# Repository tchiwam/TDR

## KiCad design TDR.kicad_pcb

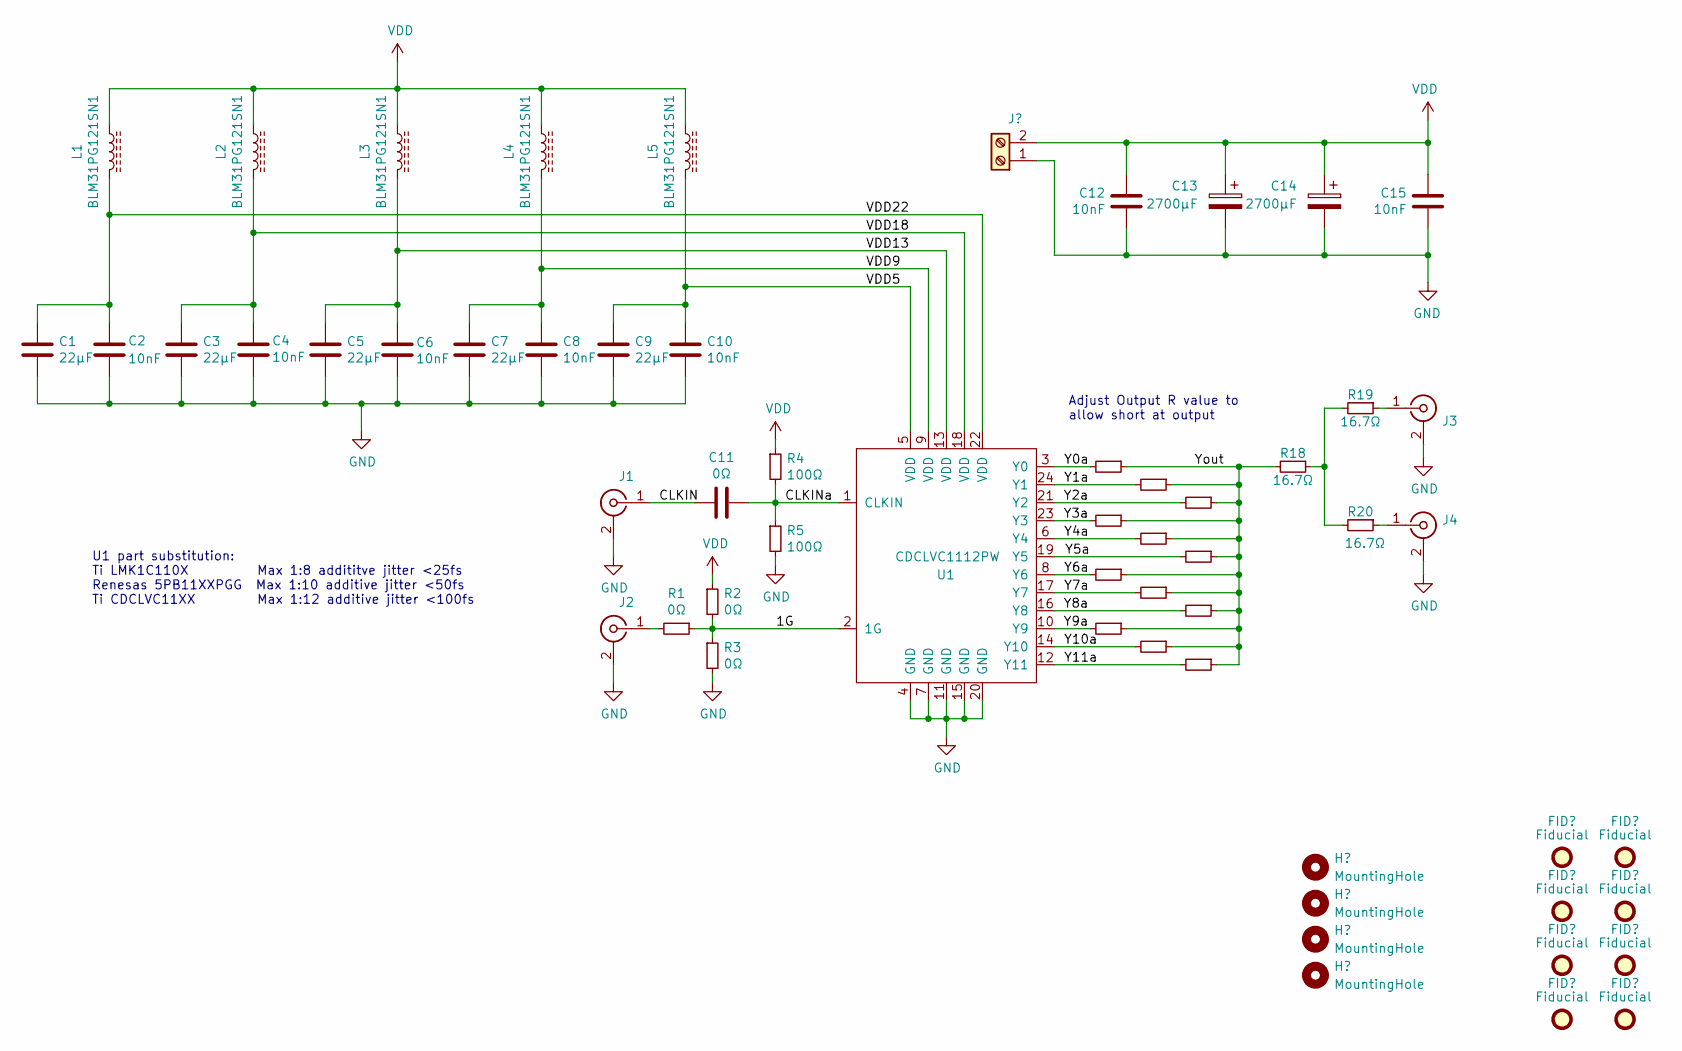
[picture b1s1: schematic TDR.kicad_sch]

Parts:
C1, C3, C5, C7, C9: 22µF; C_1206_3216Metric; PartNumber LMK316AB7226KL-TR
C2, C4, C6, C8, C10, C12, C15: 10nF; C_0402_1005Metric; PartNumber 0402ZC103JAT2A
C11: 0Ω; C_0402_1005Metric; PartNumber ERJ-2GE0R00X
C13, C14: 2700µF; CP_Elec_10x12.6; PartNumber PCG0G272MCL1GS
J1: Conn_Coaxial; SMA_Molex_73251-2123_EdgeMount_Horizontal; PartNumber 73412-0110
J2: Conn_Coaxial; U.FL_Molex_MCRF_73412-0110_Vertical; PartNumber 73412-0110
J3, J4: Conn_Coaxial; SMA_Molex_73251-2123_EdgeMount_Horizontal; PartNumber 73251-2123
L1, L2, L3, L4, L5: BLM31PG121SN1; L_1206_3216Metric; PartNumber ILHB1206ER121V
R1, R2, R3: 0Ω; R_0402_1005Metric; PartNumber ERJ-2GE0R00X
R4, R5: 100Ω; R_0402_1005Metric; PartNumber CR0402-16W-1000FT
R6, R7, R8, R9, R10, R11, R12, R13, R14, R15, R16, R17: 421Ω; R_0402_1005Metric; PartNumber ERJ-2GEJ100X
R18: 16.7Ω; R_1210_3225Metric; PartNumber ERJ-2GEJ100X
R19, R20: 16.7Ω; R_0805_2012Metric; PartNumber ERJ-2GEJ100X
U1: CDCLVC1112PW‎; TSSOP-24_4.4x7.8mm_P0.65mm; PartNumber CDCLVC1112PW‎

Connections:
/1G: R1.1, R2.2, R3.1, U1.2 (1G)
/CLKIN: C11.2, J1.1 (In)
/CLKINa: C11.1, R4.2, R5.1, U1.1 (CLKIN)
/VDD5: C9.1, C10.1, L5.2, U1.5 (VDD)
/VDD9: C7.1, C8.1, L4.2, U1.9 (VDD)
/VDD13: C5.1, C6.1, L3.2, U1.13 (VDD)
/VDD18: C3.1, C4.1, L2.2, U1.18 (VDD)
/VDD22: C1.1, C2.1, L1.2, U1.22 (VDD)
/Y0a: R6.2, U1.3 (Y0)
/Y1a: R10.2, U1.24 (Y1)
/Y2a: R14.2, U1.21 (Y2)
/Y3a: R7.2, U1.23 (Y3)
/Y4a: R11.2, U1.6 (Y4)
/Y5a: R15.2, U1.19 (Y5)
/Y6a: R8.2, U1.8 (Y6)
/Y7a: R12.2, U1.17 (Y7)
/Y8a: R16.2, U1.16 (Y8)
/Y9a: R9.2, U1.10 (Y9)
/Y10a: R13.2, U1.14 (Y10)
/Y11a: R17.2, U1.12 (Y11)
/Yout: R6.1, R7.1, R8.1, R9.1, R10.1, R11.1, R12.1, R13.1, R14.1, R15.1, R16.1, R17.1, R18.2
GND: C1.2, C2.2, C3.2, C4.2, C5.2, C6.2, C7.2, C8.2, C9.2, C10.2, C12.2, C13.2, C14.2, C15.2, J1.2 (Ext), J2.2 (Ext), J3.2 (Ext), J4.2 (Ext), R3.2, R5.2, U1.4 (GND), U1.7 (GND), U1.11 (GND), U1.15 (GND), U1.20 (GND); also elsewhere on the board
unnamed: J2.1 (In), R1.2
unnamed: J3.1 (In), R19.1
unnamed: J4.1 (In), R20.1
unnamed: R18.1, R19.2, R20.2
VDD: C12.1, C13.1, C14.1, C15.1, L1.1, L2.1, L3.1, L4.1, L5.1, R2.1, R4.1; also elsewhere on the board

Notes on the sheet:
U1 part substitution: Ti LMK1C110X Max 1:8 addititve jitter <25fs Renesas 5PB11XXPGG Max 1:10 additive jitter <50fs Ti CDCLVC11XX Max 1:12 additive jitter <100fs
Adjust Output R value to allow short at output

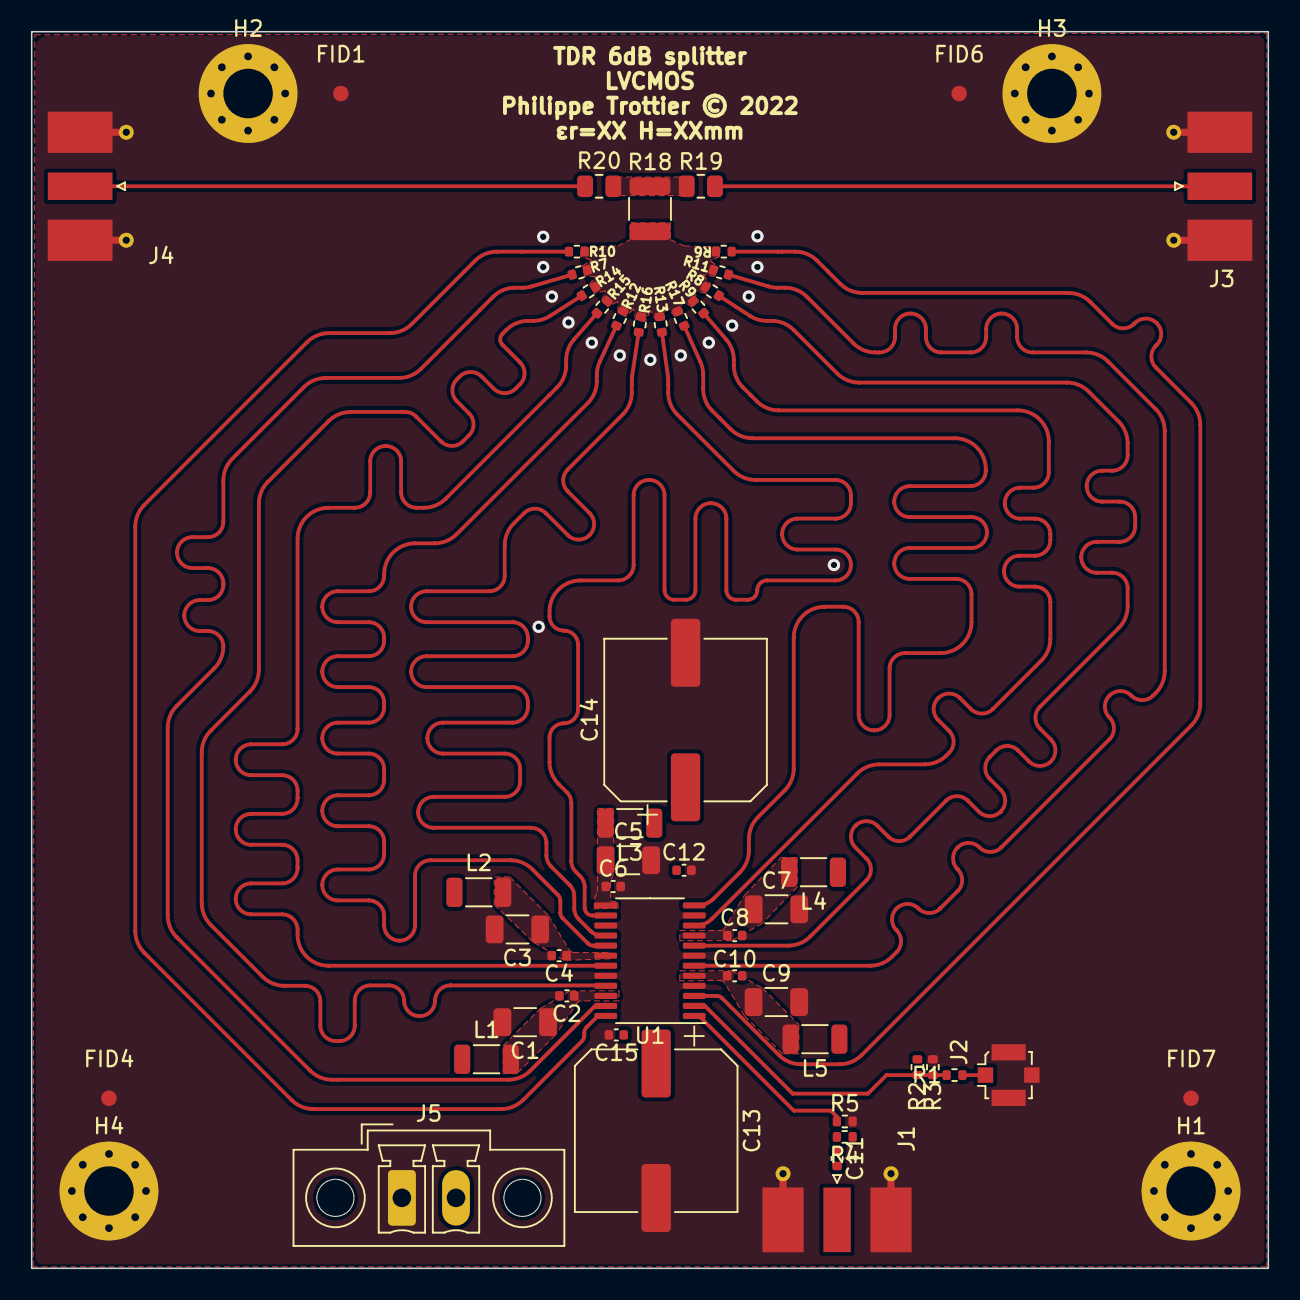
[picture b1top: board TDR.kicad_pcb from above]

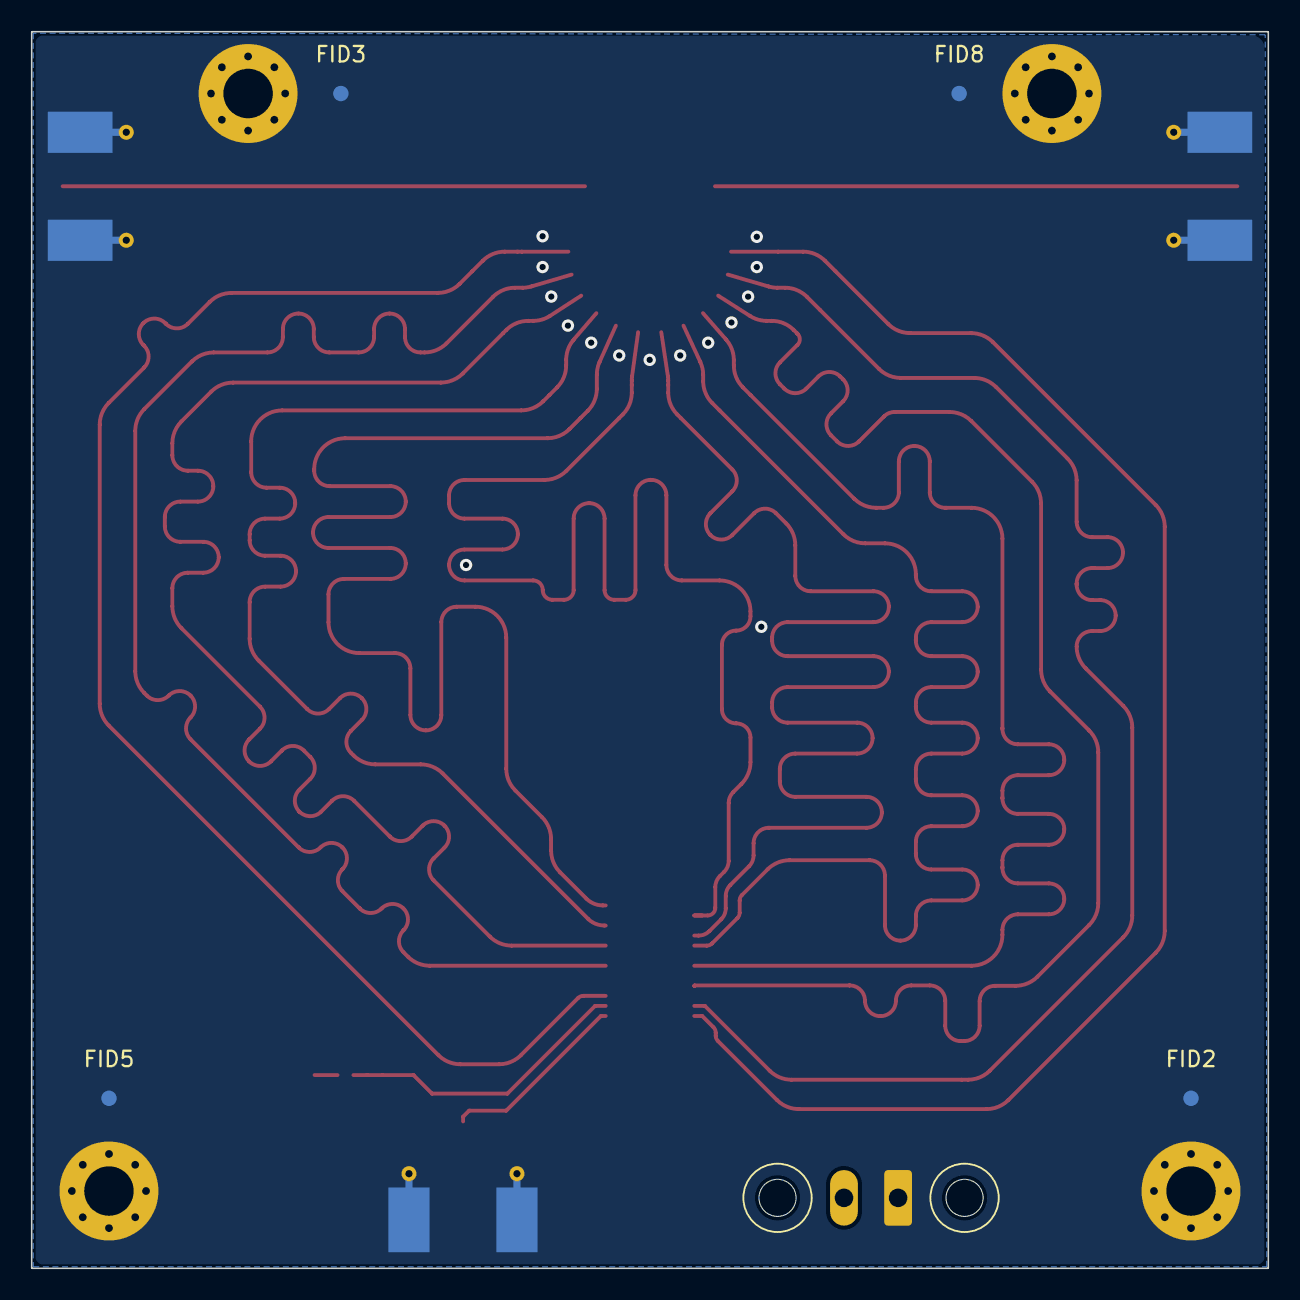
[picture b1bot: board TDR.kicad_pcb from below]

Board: 4 copper layers, 80.0 x 80.0 mm, 58 parts (4 on the bottom side), 27 nets.

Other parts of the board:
FID1, FID2, FID3, FID4, FID5, FID6, FID7, FID8: Fiducial; Fiducial_1mm_Mask3mm
H1, H2, H3, H4: MountingHole; MountingHole_3.2mm_M3_Pad_Via
J5: Screw_Terminal_01x02; PhoenixContact_MCV_1,5_2-GF-3.5_1x02_P3.50mm_Vertical_Threa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

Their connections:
GND: J5.1; also elsewhere on the board
VDD: J5.2; also elsewhere on the board

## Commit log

2022-07-23 initial hello
2022-07-23 pretty
2022-07-23 TDR fun

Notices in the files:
TDR.kicad_pcb:
Philippe Trottier © 2022
